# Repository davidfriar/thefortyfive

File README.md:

# Introduction

This is ***The Forty Five***, an open source forty five percent mechanical keyboard, allegedly designed by Old Badger.

Some of the  key features are:

- Fully programmable using QMK
- Staggered 45 key layout
- Connects via Bluetooth (BLE) or via USB C
- Internal 1200Mah LIPO battery (120 hours continuous use from a 12 hour charge)
- Charges via USB C while plugged in

# Project Goals

## If you're new to the world of custom keyboards

# Build notes

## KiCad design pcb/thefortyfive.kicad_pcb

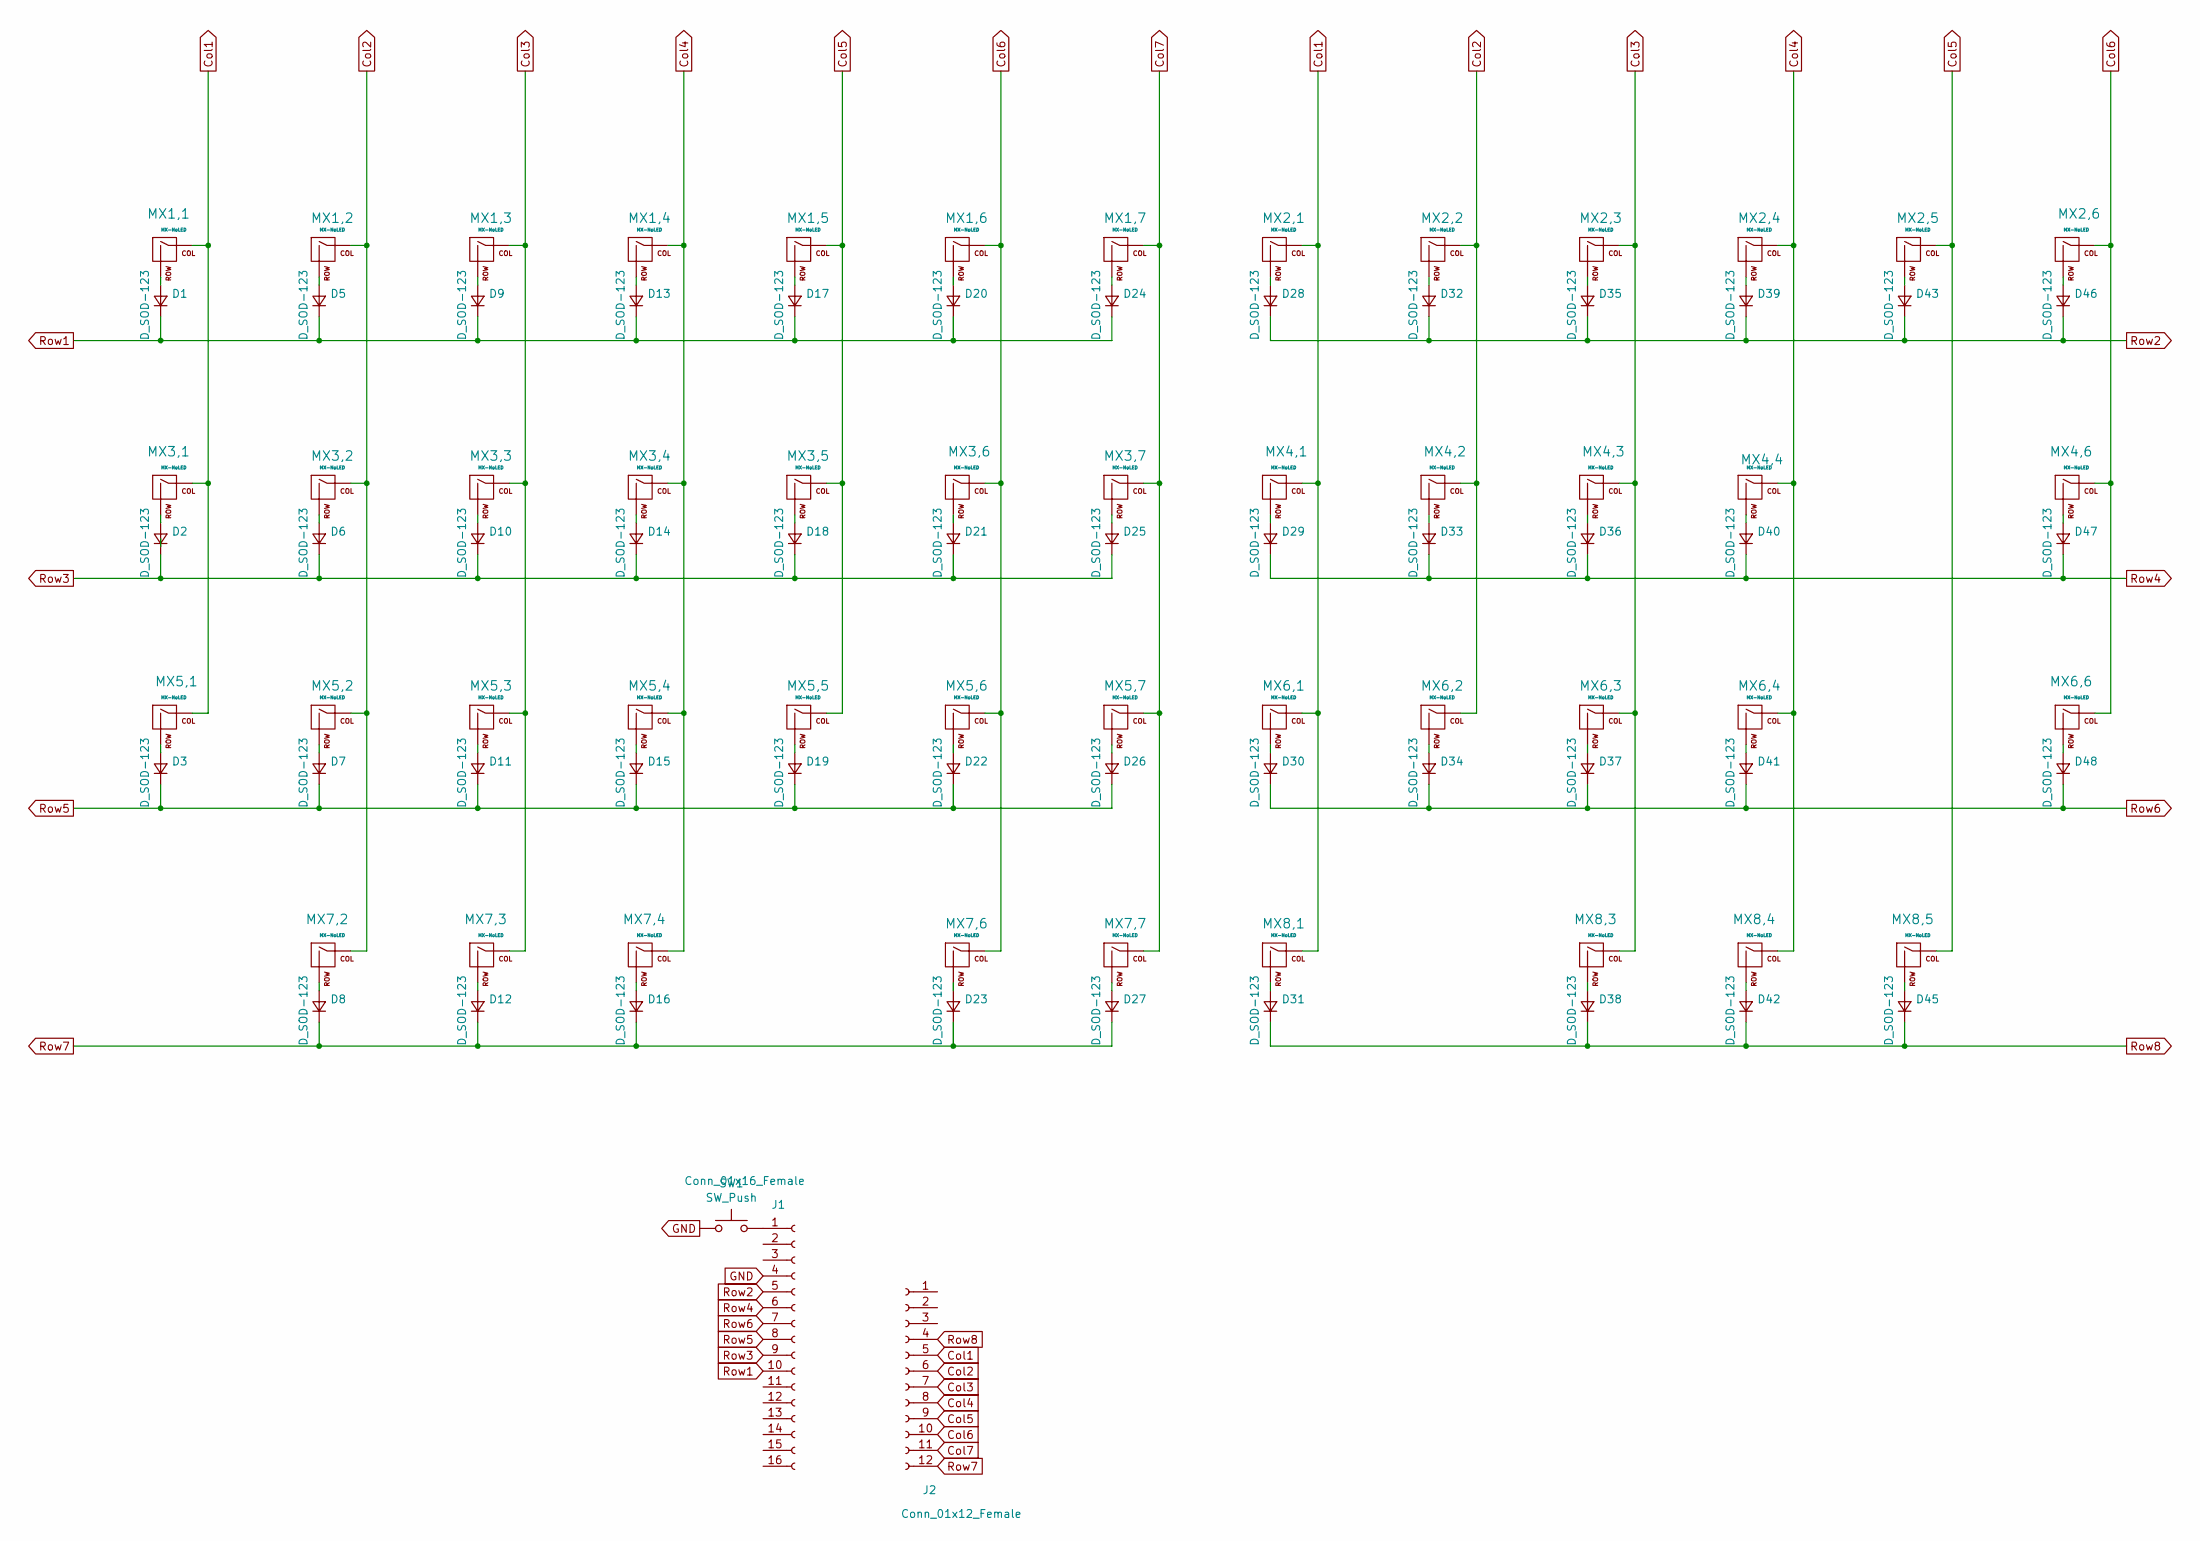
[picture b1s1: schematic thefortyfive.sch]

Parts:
D1, D2, D3, D5, D6, D7, D8, D9, D10, D11, D12, D13, D14, D15, D16, D17, D18, D19, D20, D21, D22, D23, D24, D25, D26, D27, D28, D29, D30, D31, D32, D33, D34, D35, D36, D37, D38, D39, D40, D41, D42, D43, D45, D46, D47, D48: D_SOD-123
J1: Conn_01x16_Female; PinSocket_1x16_P2.54mm_Vertical
J2: Conn_01x12_Female; PinSocket_1x12_P2.54mm_Vertical
MX1,1, MX1,2, MX1,3, MX1,4, MX1,5, MX1,6, MX1,7, MX2,1, MX2,2, MX2,3, MX2,4, MX2,5, MX2,6, MX3,2, MX3,3, MX3,4, MX3,5, MX3,6, MX3,7, MX4,1, MX4,2, MX4,3, MX4,4, MX5,2, MX5,3, MX5,4, MX5,5, MX5,6, MX5,7, MX6,1, MX6,2, MX6,3, MX6,4, MX7,2, MX7,4, MX8,3, MX8,5: MX-NoLED; MXOnly-1U-NoLED
MX3,1, MX6,6, MX7,3, MX8,4: MX-NoLED; MXOnly-1.25U-NoLED
MX4,6, MX5,1: MX-NoLED; MXOnly-1.75U-NoLED
MX7,6: MX-NoLED; MXOnly-2.25U-NoLED
MX7,7: MX-NoLED; MXOnly-7U-NoLED
MX8,1: MX-NoLED; MXOnly-2.75U-NoLED
SW1: SW_Push; SW_SPST_B3U-1100P

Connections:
Col1: J2.5, MX1,1.1 (COL), MX2,1.1 (COL), MX3,1.1 (COL), MX4,1.1 (COL), MX5,1.1 (COL), MX6,1.1 (COL), MX8,1.1 (COL)
Col2: J2.6, MX1,2.1 (COL), MX2,2.1 (COL), MX3,2.1 (COL), MX4,2.1 (COL), MX5,2.1 (COL), MX6,2.1 (COL), MX7,2.1 (COL)
Col3: J2.7, MX1,3.1 (COL), MX2,3.1 (COL), MX3,3.1 (COL), MX4,3.1 (COL), MX5,3.1 (COL), MX6,3.1 (COL), MX7,3.1 (COL), MX8,3.1 (COL)
Col4: J2.8, MX1,4.1 (COL), MX2,4.1 (COL), MX3,4.1 (COL), MX4,4.1 (COL), MX5,4.1 (COL), MX6,4.1 (COL), MX7,4.1 (COL), MX8,4.1 (COL)
Col5: J2.9, MX1,5.1 (COL), MX2,5.1 (COL), MX3,5.1 (COL), MX5,5.1 (COL), MX8,5.1 (COL)
Col6: J2.10, MX1,6.1 (COL), MX2,6.1 (COL), MX3,6.1 (COL), MX4,6.1 (COL), MX5,6.1 (COL), MX6,6.1 (COL), MX7,6.1 (COL)
Col7: J2.11, MX1,7.1 (COL), MX3,7.1 (COL), MX5,7.1 (COL), MX7,7.1 (COL)
GND: J1.4, SW1.1
unnamed: D1.2 (A), MX1,1.2 (ROW)
unnamed: D2.2 (A), MX3,1.2 (ROW)
unnamed: D3.2 (A), MX5,1.2 (ROW)
unnamed: D5.2 (A), MX1,2.2 (ROW)
unnamed: D6.2 (A), MX3,2.2 (ROW)
unnamed: D7.2 (A), MX5,2.2 (ROW)
unnamed: D8.2 (A), MX7,2.2 (ROW)
unnamed: D9.2 (A), MX1,3.2 (ROW)
unnamed: D10.2 (A), MX3,3.2 (ROW)
unnamed: D11.2 (A), MX5,3.2 (ROW)
unnamed: D12.2 (A), MX7,3.2 (ROW)
unnamed: D13.2 (A), MX1,4.2 (ROW)
unnamed: D14.2 (A), MX3,4.2 (ROW)
unnamed: D15.2 (A), MX5,4.2 (ROW)
unnamed: D16.2 (A), MX7,4.2 (ROW)
unnamed: D17.2 (A), MX1,5.2 (ROW)
unnamed: D18.2 (A), MX3,5.2 (ROW)
unnamed: D19.2 (A), MX5,5.2 (ROW)
unnamed: D20.2 (A), MX1,6.2 (ROW)
unnamed: D21.2 (A), MX3,6.2 (ROW)
unnamed: D22.2 (A), MX5,6.2 (ROW)
unnamed: D23.2 (A), MX7,6.2 (ROW)
unnamed: D24.2 (A), MX1,7.2 (ROW)
unnamed: D25.2 (A), MX3,7.2 (ROW)
unnamed: D26.2 (A), MX5,7.2 (ROW)
unnamed: D27.2 (A), MX7,7.2 (ROW)
unnamed: D28.2 (A), MX2,1.2 (ROW)
unnamed: D29.2 (A), MX4,1.2 (ROW)
unnamed: D30.2 (A), MX6,1.2 (ROW)
unnamed: D31.2 (A), MX8,1.2 (ROW)
unnamed: D32.2 (A), MX2,2.2 (ROW)
unnamed: D33.2 (A), MX4,2.2 (ROW)
unnamed: D34.2 (A), MX6,2.2 (ROW)
unnamed: D35.2 (A), MX2,3.2 (ROW)
unnamed: D36.2 (A), MX4,3.2 (ROW)
unnamed: D37.2 (A), MX6,3.2 (ROW)
unnamed: D38.2 (A), MX8,3.2 (ROW)
unnamed: D39.2 (A), MX2,4.2 (ROW)
unnamed: D40.2 (A), MX4,4.2 (ROW)
unnamed: D41.2 (A), MX6,4.2 (ROW)
unnamed: D42.2 (A), MX8,4.2 (ROW)
unnamed: D43.2 (A), MX2,5.2 (ROW)
unnamed: D45.2 (A), MX8,5.2 (ROW)
unnamed: D46.2 (A), MX2,6.2 (ROW)
unnamed: D47.2 (A), MX4,6.2 (ROW)
unnamed: D48.2 (A), MX6,6.2 (ROW)
unnamed: J1.1, SW1.2
Row1: D1.1 (K), D5.1 (K), D9.1 (K), D13.1 (K), D17.1 (K), D20.1 (K), D24.1 (K), J1.10
Row2: D28.1 (K), D32.1 (K), D35.1 (K), D39.1 (K), D43.1 (K), D46.1 (K), J1.5
Row3: D2.1 (K), D6.1 (K), D10.1 (K), D14.1 (K), D18.1 (K), D21.1 (K), D25.1 (K), J1.9
Row4: D29.1 (K), D33.1 (K), D36.1 (K), D40.1 (K), D47.1 (K), J1.6
Row5: D3.1 (K), D7.1 (K), D11.1 (K), D15.1 (K), D19.1 (K), D22.1 (K), D26.1 (K), J1.8
Row6: D30.1 (K), D34.1 (K), D37.1 (K), D41.1 (K), D48.1 (K), J1.7
Row7: D8.1 (K), D12.1 (K), D16.1 (K), D23.1 (K), D27.1 (K), J2.12
Row8: D31.1 (K), D38.1 (K), D42.1 (K), D45.1 (K), J2.4

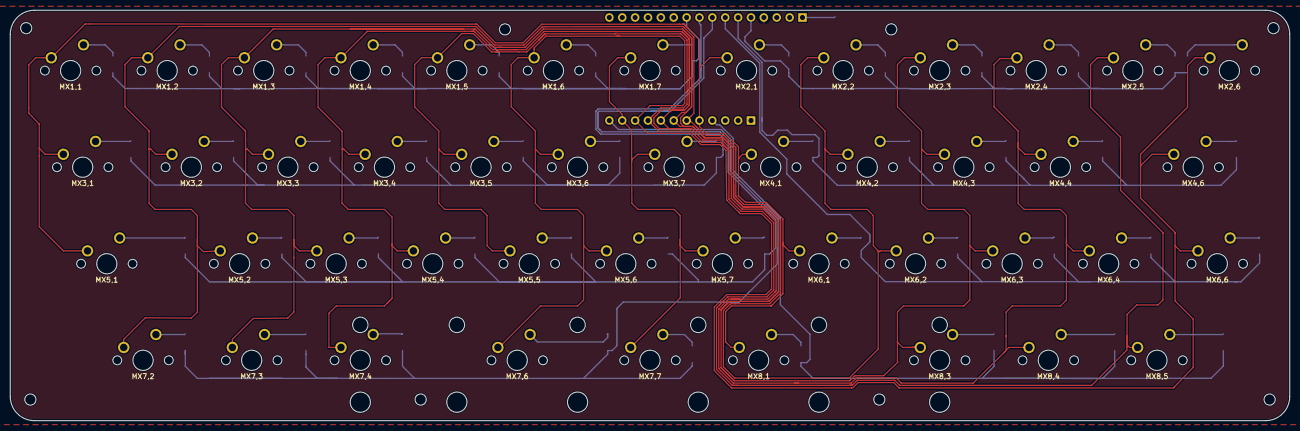
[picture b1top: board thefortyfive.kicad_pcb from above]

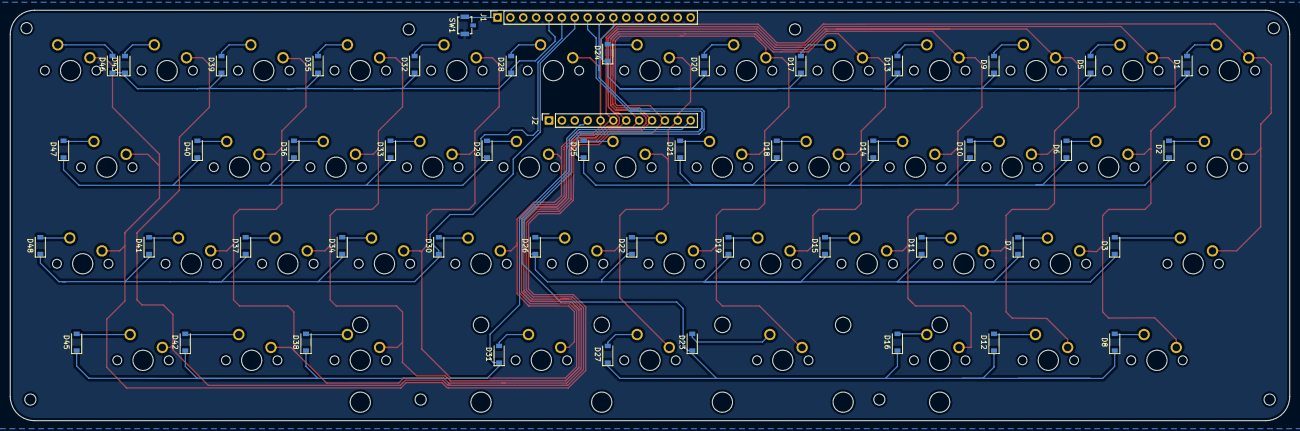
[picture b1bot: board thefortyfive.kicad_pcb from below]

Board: 2 copper layers, 252.4 x 81.0 mm, 95 parts (49 on the bottom side), 63 nets.

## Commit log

2020-03-14 add pcb project
2020-03-14 add MX switch library submodule
2020-03-14 add library to kicad
2020-03-14 add gitignore for kicad
2020-03-14 added basic key matrix, no optional keys
2020-03-15 add switch and plate experiments
2020-03-15 add optional switches
2020-03-15 add sizing for switch footprints
2020-03-15 add edge cut
2020-03-15 updated footprints
2020-03-15 removed led pads from some footprints
2020-03-15 added diodes
2020-03-17 add routing
2020-03-18 move diodes out of breakaway zone
2020-03-18 add ground fills
2020-03-19 add switch labels
2020-03-21 add title, reduce width
2020-03-31 configure gerbers
2020-03-31 fix issue with reversed connector
2020-04-03 change plate layer
2020-04-03 add art
2020-04-03 ignore todo
2020-04-03 remove all switch options
2020-04-04 reduce width, update version message
2020-04-04 reroute tracks away from edges
2020-04-05 added reset button
2020-04-05 adjust routing around mounting holes
2020-04-05 reposition mounting holes
2020-04-05 adjust lettering
2020-04-06 add bottom plate
2020-04-06 add reset button to schema
2020-04-10 add art, tweak mounting holes
2020-04-10 add paw
2020-04-10 tweak positioning
2020-04-11 split pcb project
2020-04-11 add gerber files
2020-04-11 fix origins, export to step, convert to stl, create openscad
2020-04-11 create basic shape
2020-04-12 add clearance holes
2020-04-18 add name and other design changes
2020-04-18 add gaps for usb and controller. improved clearance holes
2020-04-30 clean up code ready for v2
2020-04-30 make holes deeper for threaded inserts
2020-04-30 add hole to clear diode
2020-04-30 add more clearance for stabilisers, remove redundant clearance holes
2020-04-30 add better clearance for usb bolts and resistor on usb board
2020-05-15 add read me
2020-05-15 add gerberstmp to ignore
2020-05-15 add keycaps
2020-05-15 cleanup
2020-05-15 add some svgs
2020-09-06 trying to fix submodules
2020-09-06 removed pcb submodules
2020-09-06 fixed submodules
